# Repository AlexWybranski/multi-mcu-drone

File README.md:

# multi-mcu-drone

#### Disclaimer
- Due to free profiles of HICPP and CPPCOREGUIDELINES in clang-tidy, this code is supposed to be taken as "HICPP-ish verified"
- **Current State:** Firmware is tested on hardware prototype (most of that (branch feature-uart-for-esc is untested) has been written to this day (**5 Nov 2026**)), buck converter burned out and took esp32c6-receiver with itself 

## System overview
This firmware is written primarily in C++. The general description of the software modules for each specific board is detailed below (**Detailed overview of mcus' firmwares can be found in respective README files in mcu specific folders**):

- [esp32c6-rc](esp32c6-rc/) - Remote control module; handles gamepad input and transmits data wirelessly to the drone via the ESP-NOW protocol.
- [esp32c6-receiver](esp32c6-receiver/) - Receiver module; captures ESP-NOW packets, forwards them to the [stm32f4-main](stm32f4-main/) module via UART, and generates PWM signal for camera servo control.
- [stm32f4-main](stm32f4-main/) - Flight controller; Main core of the drone. Runs a **completely custom-written HAL layer (bare-metal drivers, custom startup code, and self written linker script) and tailor-made DMA IRQs (more in [README file](stm32f4-main/README.md))**. Receives packets via **UART with DMA**. Calculates PID, handle motor mixer logic and generates high-frequency PWM duty cycles based on gamepad input and SPI-sampled IMU data (accelerometer/gyroscope).

## Data flow
```mermaid
flowchart LR
%%{init: { 'flowchart': { 'curve': 'stepAfter' }, 'themeCSS': '.edgePath .path { stroke-linejoin: miter; stroke-linecap: square; }' } }%%
    A[Remote Control] 
    B[RECEIVER]
    C[FLIGHT CONTROLLER]
    D[SENSOR]
    E[ESC]
    %% F[SERVO]
    %% G[CAM]
    %% H[HTTP SERVER - VIDEO STREAM]

    A -.->|ESP-NOW| B
    %% G -.-> H
    subgraph On Drone
    B -->|UART| C
    %% B -->|PWM| F ===|PHYSICAL CONNECTION|G
    C <-->|SPI| D
    C -->|PWM| E
    E -->|UART| C
    end
```

## Third-party code
This project uses: 
- **[Bluepad32](https://github.com/ricardoquesada/bluepad32)** and its dependency **[BTStack](https://github.com/bluekitchen/btstack)** - Licensed under Apache 2.0 license
- **[FreeRTOS](https://github.com/freertos)** - Licensed under MIT license
- **STMicroelectronics System Files** ([stm32f4-main/src/syscalls.c](stm32f4-main/src/syscalls.c)): 
   Copyright (c) STMicroelectronics. Provided "AS-IS" under the vendor's standard 
   evaluation software license agreement terms embedded within the file header.
- **Espressif ESP-IDF Components** - Licensed mostly under Apache 2.0 license

More about licensing and conditions in [LICENSE-3RD-PARTY](https://github.com/AlexWybranski/multi-mcu-drone/blob/master/LICENSE-3RD-PARTY.md)

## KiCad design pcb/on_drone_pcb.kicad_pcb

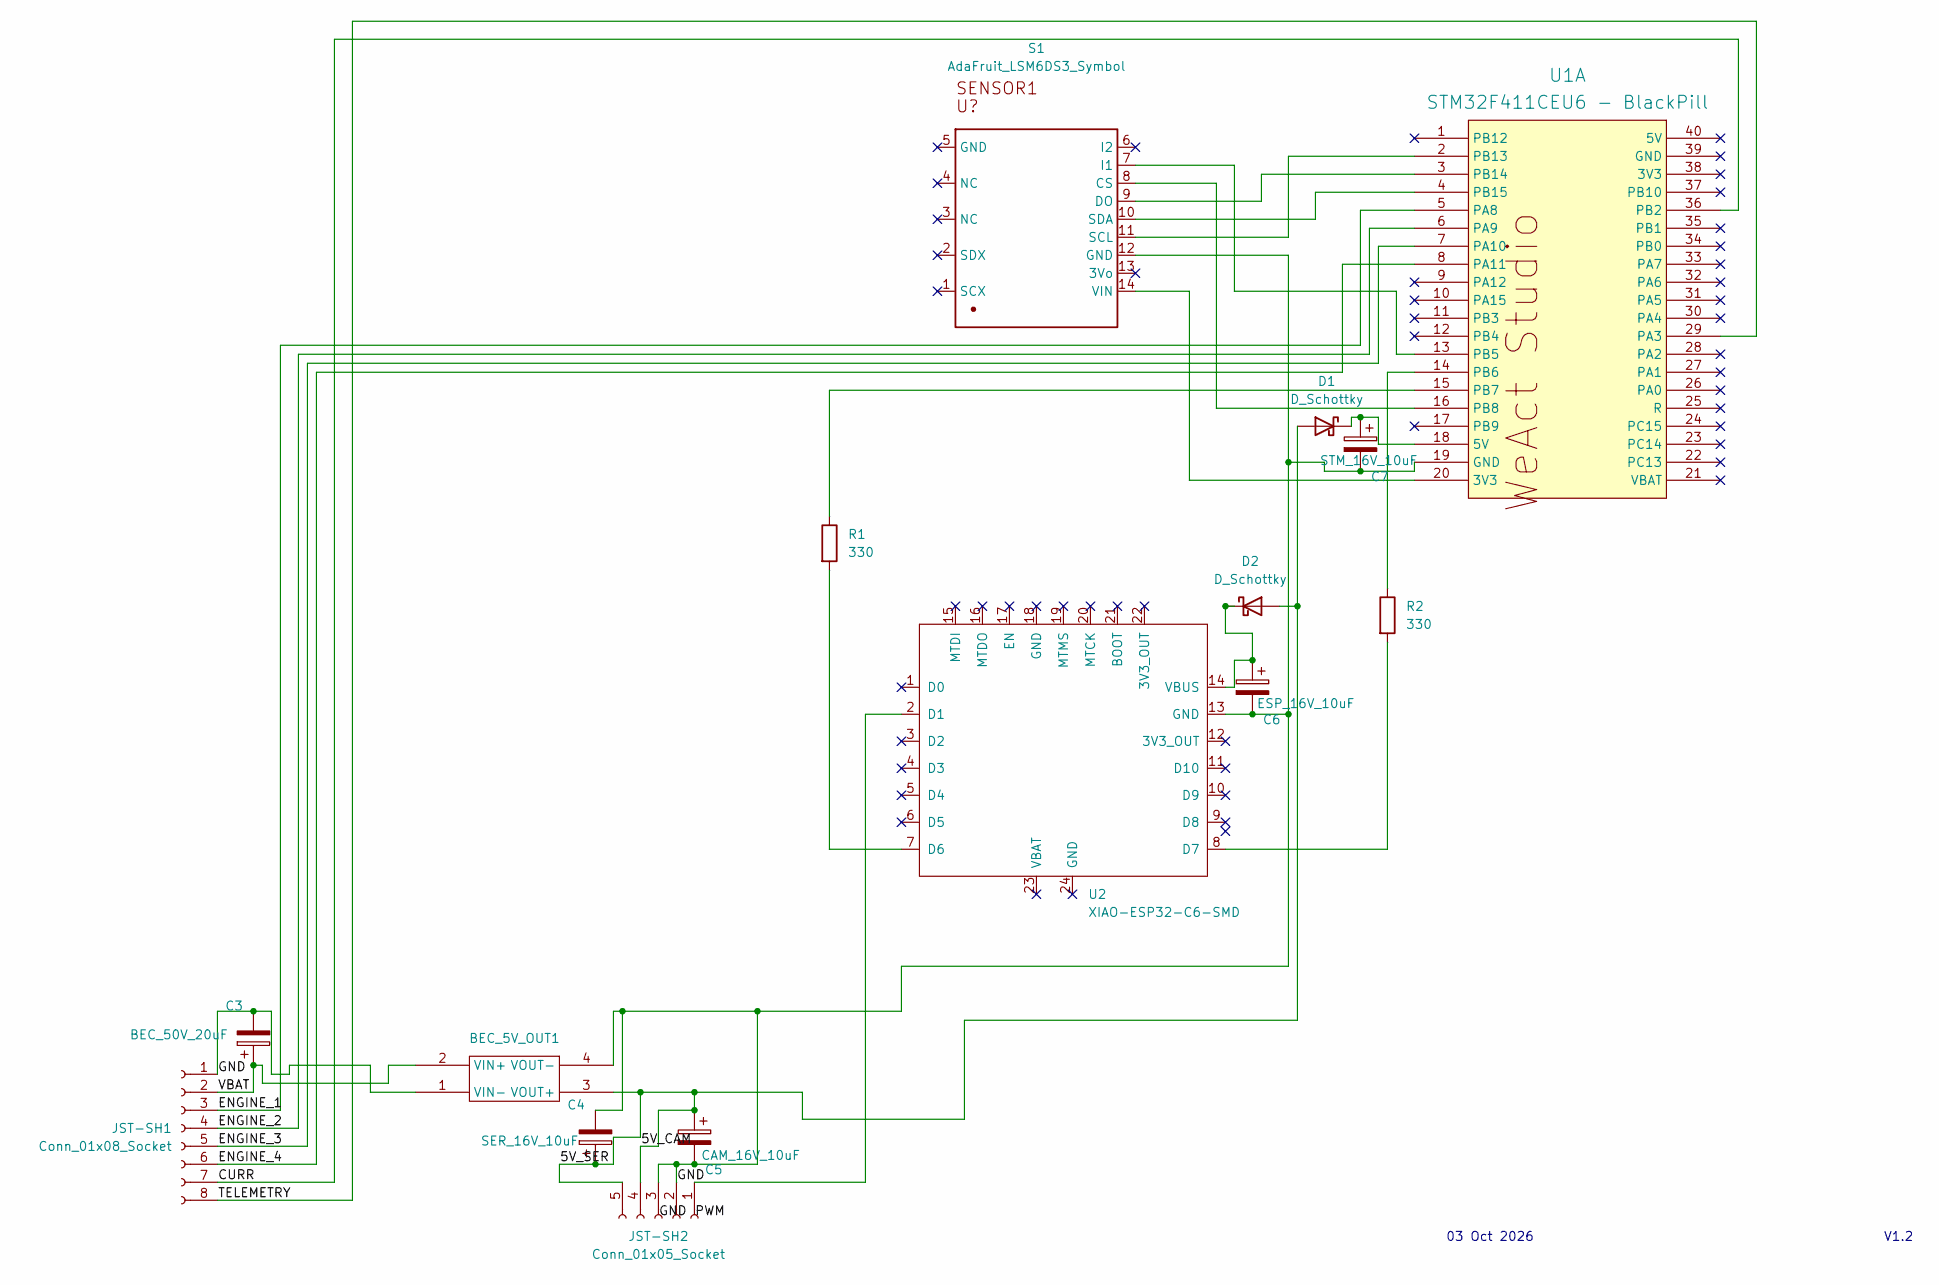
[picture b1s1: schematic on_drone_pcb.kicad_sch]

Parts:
BEC_5V_OUT1: PinHeader_2x02_P2.54mm_Vertical_SMD
C3: BEC_50V_20uF; CP_EIA-6032-28_Kemet-C_HandSolder
C4: SER_16V_10uF; C_1206_3216Metric_Pad1.33x1.80mm_HandSolder
C5: CAM_16V_10uF; C_1206_3216Metric_Pad1.33x1.80mm_HandSolder
C6: ESP_16V_10uF; C_1206_3216Metric_Pad1.33x1.80mm_HandSolder
C7: STM_16V_10uF; C_1206_3216Metric_Pad1.33x1.80mm_HandSolder
D1, D2: D_Schottky; D_SOD-123
JST-SH1: Conn_01x08_Socket; JST_XH_S8B-XH-A_1x08_P2.50mm_Horizontal
JST-SH2: Conn_01x05_Socket; JST_XH_S5B-XH-A_1x05_P2.50mm_Horizontal
R1, R2: 330; R_0805_2012Metric_Pad1.20x1.40mm_HandSolder
S1: AdaFruit_LSM6DS3_Symbol; imu_footprint
U1: STM32F411CEU6 - BlackPill; BlackPill AT32F403ACx WeActStudio
U2: XIAO-ESP32-C6-SMD; XIAO-ESP32-C6-DIP

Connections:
/5V_CAM: BEC_5V_OUT1.3 (VOUT+), C4.1, C5.1, D1.2 (A), D2.2 (A), JST-SH2.4, JST-SH2.5
/CURR: JST-SH1.7, U1.36 (PB2)
/ENGINE_1: JST-SH1.3, U1.5 (PA8)
/ENGINE_2: JST-SH1.4, U1.6 (PA9)
/ENGINE_3: JST-SH1.5, U1.7 (PA10)
/ENGINE_4: JST-SH1.6, U1.8 (PA11)
/GND: BEC_5V_OUT1.1 (VIN-), BEC_5V_OUT1.4 (VOUT-), C3.2, C4.2, C5.2, C6.2, C7.2, JST-SH1.1, JST-SH2.2, JST-SH2.3, S1.12 (GND), U1.19 (GND), U2.13 (GND)
/TELEMETRY: JST-SH1.8, U1.29 (PA3)
/VBAT: BEC_5V_OUT1.2 (VIN+), C3.1, JST-SH1.2
unnamed: C7.1, D1.1 (K), U1.18 (5V)
unnamed: C6.1, D2.1 (K), U2.14 (VBUS)
unnamed: JST-SH2.1, U2.2 (D1)
unnamed: S1.8 (CS), U1.16 (PB8)
unnamed: S1.9 (DO), U1.3 (PB14)
unnamed: S1.7 (I1), U1.13 (PB5)
unnamed: S1.11 (SCL), U1.2 (PB13)
unnamed: S1.10 (SDA), U1.4 (PB15)
unnamed: S1.14 (VIN), U1.20 (3V3)
unnamed: R2.1, U1.14 (PB6)
unnamed: R1.1, U1.15 (PB7)
unnamed: R1.2, U2.7 (D6)
unnamed: R2.2, U2.8 (D7)

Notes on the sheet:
03 Oct 2026
V1.2

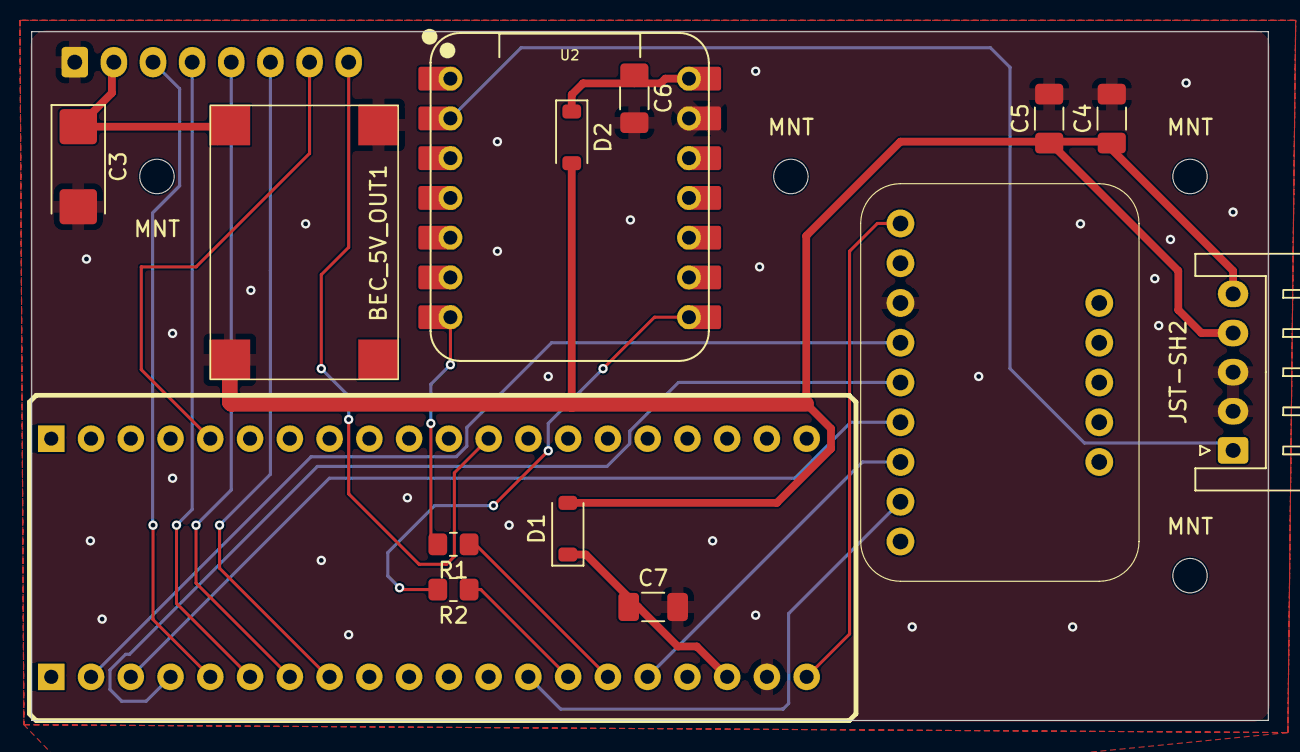
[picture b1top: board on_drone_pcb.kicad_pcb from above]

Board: 4 copper layers, 79.0 x 44.0 mm, 19 parts (1 on the bottom side), 22 nets.

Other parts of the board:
MNT: MountingHole_2.2mm_M2
MNT#2, MNT#3, MNT#4: MountingHole_2.2mm_M2

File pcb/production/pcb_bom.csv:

Designator,Footprint,Quantity,Value,LCSC Part #
BEC_5V_OUT1,PinHeader_2x02_P2.54mm_Vertical_SMD,1,~,
C3,CP_EIA-6032-28_Kemet-C_HandSolder,1,BEC_50V_20uF,
C4,1206,1,SER_16V_10uF,
C5,1206,1,CAM_16V_10uF,
C6,1206,1,ESP_16V_10uF,
C7,1206,1,STM_16V_10uF,
"D1, D2",D_SOD-123,2,D_Schottky,
JST-SH1,JST_XH_S8B-XH-A_1x08_P2.50mm_Horizontal,1,Conn_01x08_Socket,
JST-SH2,JST_XH_S5B-XH-A_1x05_P2.50mm_Horizontal,1,Conn_01x05_Socket,
"R1, R2",0805,2,330,
S1,imu_footprint,1,AdaFruit_LSM6DS3_Symbol,
U1,BlackPill AT32F403ACx WeActStudio,1,STM32F411CEU6 - BlackPill,
U2,XIAO-ESP32-C6-DIP,1,XIAO-ESP32-C6-SMD,
